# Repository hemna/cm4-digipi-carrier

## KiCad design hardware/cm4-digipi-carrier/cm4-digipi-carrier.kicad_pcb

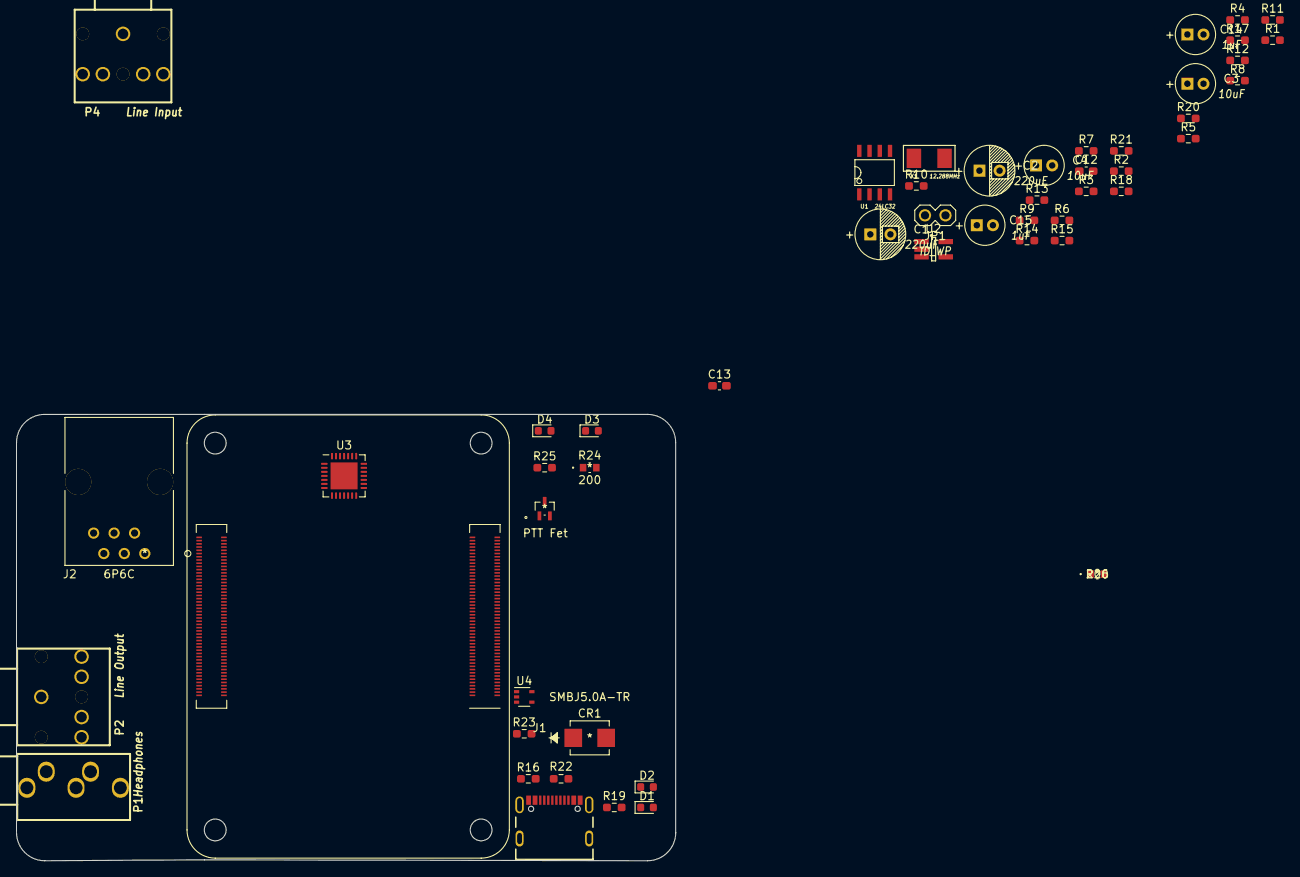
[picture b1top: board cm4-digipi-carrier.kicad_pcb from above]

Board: 2 copper layers, 81.8 x 55.4 mm, 52 parts (0 on the bottom side), 52 nets, no tracks yet.

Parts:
C1, C2: 220uF; Cap_Elec_Radial_6.3mm
C3, C4: 10uF; Cap_Elec_Radial_5mm
C12, C13: 22pF; C_0603_1608Metric_Pad1.08x0.95mm_HandSolder
C14, C15: 1uF; Cap_Elec_Radial_5mm
CR1: SMBJ5.0A-TR
D1: LED Green; LED_0603_1608Metric
D2: LED Red; LED_0603_1608Metric
D3: RX LED; LED_0603_1608Metric
D4: PTT LED; LED_0603_1608Metric
J1: USB4105-GF-A; GCT_USB4105-GF-A
J2: 6P6C; SS-90000-003
JP1: ID_WP; Conn_Pin_Header_2x1_2.54mm_NoKey
MOSFET1: PTT Fet; RHU002N06FRAT106
Module1: ComputeModule4-CM4; Raspberry-Pi-4-Compute-Module
P1: Headphones; Conn_Audio_3.5mm_Stereo_SJ1-353XNG
P2: Line Output; Conn_Audio_3.5mm_Stereo
P4: Line Input; Conn_Audio_3.5mm_Stereo
R1, R2: 100; R_0603_1608Metric_Pad0.98x0.95mm_HandSolder
R3, R4, R5, R6: 47k; R_0603_1608Metric_Pad0.98x0.95mm_HandSolder
R7, R8, R9, R10, R14, R15: 33; R_0603_1608Metric_Pad0.98x0.95mm_HandSolder
R11, R19, R23: 1k; R_0603_1608Metric_Pad0.98x0.95mm_HandSolder
R12, R13: 3.9k; R_0603_1608Metric_Pad0.98x0.95mm_HandSolder
R16, R22: 5.1k; R_0603_1608Metric_Pad0.98x0.95mm_HandSolder
R17, R18, R20, R21: 5.6k; R_0603_1608Metric_Pad0.98x0.95mm_HandSolder
R24, R26: 200; ERJ3EKF2000V
R25: 100k; R_0603_1608Metric_Pad0.98x0.95mm_HandSolder
U1: 24LC32; IC_SOIC8_Narrow
U2: TPS79333DBVR; IC_SOT23-5_Hand_Soldering
U3: WM8731CLSEFL; QFN-28-1EP_5x5mm_P0.5mm_EP3.35x3.35mm
U4: 74LVC1G07SE-7; SOT-353_SC-70-5
X1: 12.288MHz; Crystal_5.0x3.2mm

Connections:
+1.8V: Module1.88 (+1.8v_(Output)), Module1.90 (+1.8v_(Output))
+3.3V: D1.2 (A), D2.2 (A), Module1.84 (+3.3v_(Output)), Module1.86 (+3.3v_(Output)), R11.2, R12.2, R13.2, U1.8 (VCC), U3.3 (DCVDD), U3.5 (DBVDD), U4.5 (VCC)
+5V: CR1.1, Module1.77 (+5v_(Input)), Module1.79 (+5v_(Input)), Module1.81 (+5v_(Input)), Module1.83 (+5v_(Input)), Module1.85 (+5v_(Input)), Module1.87 (+5v_(Input)), U2.1 (IN), U2.3 (EN)
/CM4 GPIO/nLED_Activity: Module1.21 (PI_nLED_Activity), R19.2
/CM4 GPIO/nPWR_LED: Module1.95 (nPI_LED_PWR), U4.2
AVDD: U2.5 (OUT), U3.12 (HPVDD), U3.18 (AVDD)
Audio from Radio: J2.6, P4.5, R20.2
Audio to Radio: J2.5, P2.5, R1.1
GND: C12.2, C13.2, CR1.2, J2.1, J2.4, JP1.2, MOSFET1.2, Module1.1 (GND), Module1.2 (GND), Module1.7 (GND), Module1.8 (GND), Module1.13 (GND), Module1.14 (GND), Module1.22 (GND), Module1.23 (GND), Module1.32 (GND), Module1.33 (GND), Module1.42 (GND), Module1.43 (GND), Module1.52 (GND), Module1.53 (GND), Module1.59 (GND), Module1.60 (GND), Module1.65 (GND), Module1.66 (GND), Module1.71 (GND), Module1.74 (GND), Module1.98 (GND), Module1.107 (GND), Module1.108 (GND), Module1.113 (GND), Module1.114 (GND), Module1.119 (GND), Module1.120 (GND), Module1.125 (GND), Module1.126 (GND), Module1.131 (GND), Module1.132 (GND), Module1.137 (GND), Module1.138 (GND), Module1.144 (GND), Module1.150 (GND), Module1.155 (GND), Module1.156 (GND), Module1.161 (GND), Module1.162 (GND), Module1.167 (GND), Module1.168 (GND), Module1.173 (GND), Module1.174 (GND), Module1.179 (GND), Module1.180 (GND), Module1.185 (GND), Module1.186 (GND), Module1.191 (GND), Module1.192 (GND), Module1.197 (GND), Module1.198 (GND), R16.2, R22.2, R24.2, R25.1, R26.2, U1.1 (A0), U1.2 (A1), U1.3 (A2), U1.4 (GND), U2.2 (GND), U3.4 (DGND), U4.3 (GND)
GNDA: P1.1, P2.1, P4.1, R3.1, R4.1, R5.1, R6.1, R17.1, R18.1, U3.15 (HPGND), U3.19 (AGND), U3.25 (MODE), U3.26 (~CSB), U3.29 (AGND)
GPIO12: MOSFET1.1, Module1.31 (GPIO12), R25.2
GPIO16: D3.2 (A), Module1.29 (GPIO16)
GPIO18/PCM_CLK: Module1.49 (GPIO18), R7.1
GPIO19/PCM_FS: Module1.26 (GPIO19), R9.1
GPIO20/PCM_DIN: Module1.27 (GPIO20), R10.1
GPIO21/PCM_DOUT: Module1.25 (GPIO21), R8.1
GPIO26: D4.2 (A), Module1.24 (GPIO26)
ID_SC: Module1.35 (ID_SC), R12.1, U1.6 (SCL)
ID_SD: Module1.36 (ID_SD), R13.1, U1.5 (SDA)
unnamed: C1.1, U3.13 (LHPOUT)
unnamed: C1.2, P1.5, R3.2
unnamed: C2.1, U3.14 (RHPOUT)
unnamed: C2.2, P1.2, R4.2
unnamed: C3.1, U3.16 (LOUT)
unnamed: C3.2, R1.2, R5.2
unnamed: C4.1, U3.17 (ROUT)
unnamed: C4.2, R2.2, R6.2
unnamed: C12.1, U3.2 (XTO), X1.2
unnamed: C13.1, U3.1 (XTI/MCLK), X1.1
unnamed: C14.1, U3.24 (LLINEIN)
unnamed: C14.2, R17.2, R20.1
unnamed: C15.1, U3.23 (RLINEIN)
unnamed: C15.2, R18.2, R21.1
unnamed: D1.1 (K), R19.1
unnamed: D2.1 (K), R23.1
unnamed: D3.1 (K), R24.1
unnamed: D4.1 (K), R26.1
unnamed: J1.A5 (CC1), R16.1
unnamed: J1.B5 (CC2), R22.1
unnamed: JP1.1, R11.1, U1.7 (WP)
unnamed: P2.2, R2.1
unnamed: P4.2, R21.2
unnamed: R7.2, U3.7 (BCLK)
unnamed: R8.2, U3.8 (DACDAT)
unnamed: R9.2, U3.9 (DACLRC), U3.11 (ADCLRC)
unnamed: R10.2, U3.10 (ADCDAT)
unnamed: R15.2, U3.27 (SDIN)
unnamed: R23.2, U4.4
unnamed: R14.2, U3.28 (SCLK)
PTT: J2.2, MOSFET1.3
SCL: Module1.80 (SCL0), R14.1
SDA: Module1.82 (SDA0), R15.1

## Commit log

2021-11-28 Copied from rpi-cm4-carrier-template
2021-11-28 renamed
2021-12-15 Initial Commit.

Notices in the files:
hardware/cm4-digipi-carrier/cm4-digipi-carrier.kicad_pcb:
creativecommons.org/licenses/by/4.0
License: CC BY 4.0
parts and their libraries:
Copyright 2021 Accelerated Designs. All rights reserved.
